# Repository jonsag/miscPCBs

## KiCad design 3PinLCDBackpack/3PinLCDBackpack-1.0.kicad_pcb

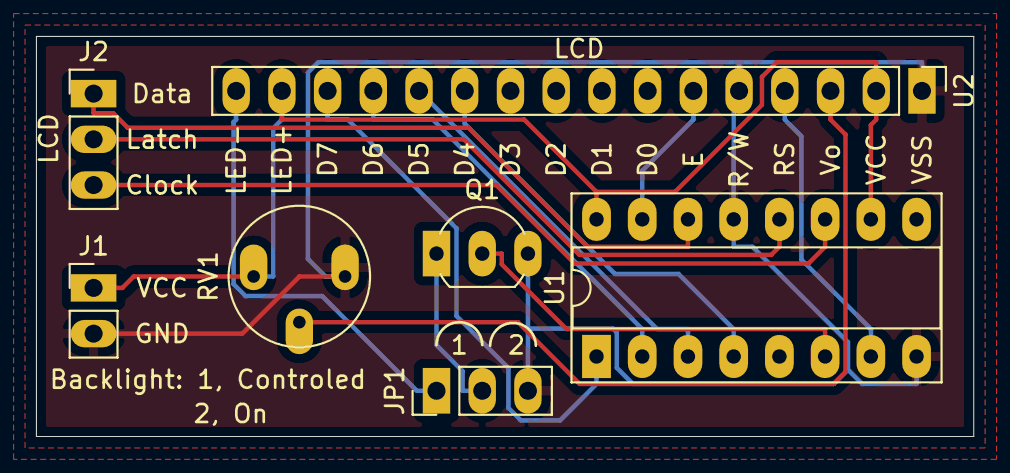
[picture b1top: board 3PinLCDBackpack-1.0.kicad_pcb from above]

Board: 2 copper layers, 52.1 x 22.2 mm, 7 parts (0 on the bottom side), 15 nets.

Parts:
J1: 2-pin_power_input_header; 2-pin_power_input_header_larger_pads
J2: 3-pin_LCD_header; 3-pin_LCD_header_larger_pads
JP1: Backlight control; Jumper_1x03_P2.54mm_large
Q1: BC547; TO-92_Inline_Wide_large
RV1: 10k; Potentiometer_Bourns_3339P_Vertical_large
U1: 74HC595; DIP-16_W7.62mm_Socket_LongPads
U2: LCD_HD44780; 16-pin_LCD_header_larger_pads

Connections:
/GND: J1.2, JP1.3, Q1.3, RV1.1, U1.8, U1.13, U2.1, U2.5
unnamed: J1.1, RV1.3, U1.10, U1.16, U2.2, U2.15
unnamed: J2.1, U1.14
unnamed: J2.2, U1.12
unnamed: J2.3, U1.11
unnamed: JP1.1, U2.16
unnamed: JP1.2, Q1.1
unnamed: Q1.2, U1.6
unnamed: RV1.2, U2.3
unnamed: U1.1, U2.14
unnamed: U1.2, U2.13
unnamed: U1.3, U2.12
unnamed: U1.4, U2.11
unnamed: U1.7, U2.4
unnamed: U1.15, U2.6

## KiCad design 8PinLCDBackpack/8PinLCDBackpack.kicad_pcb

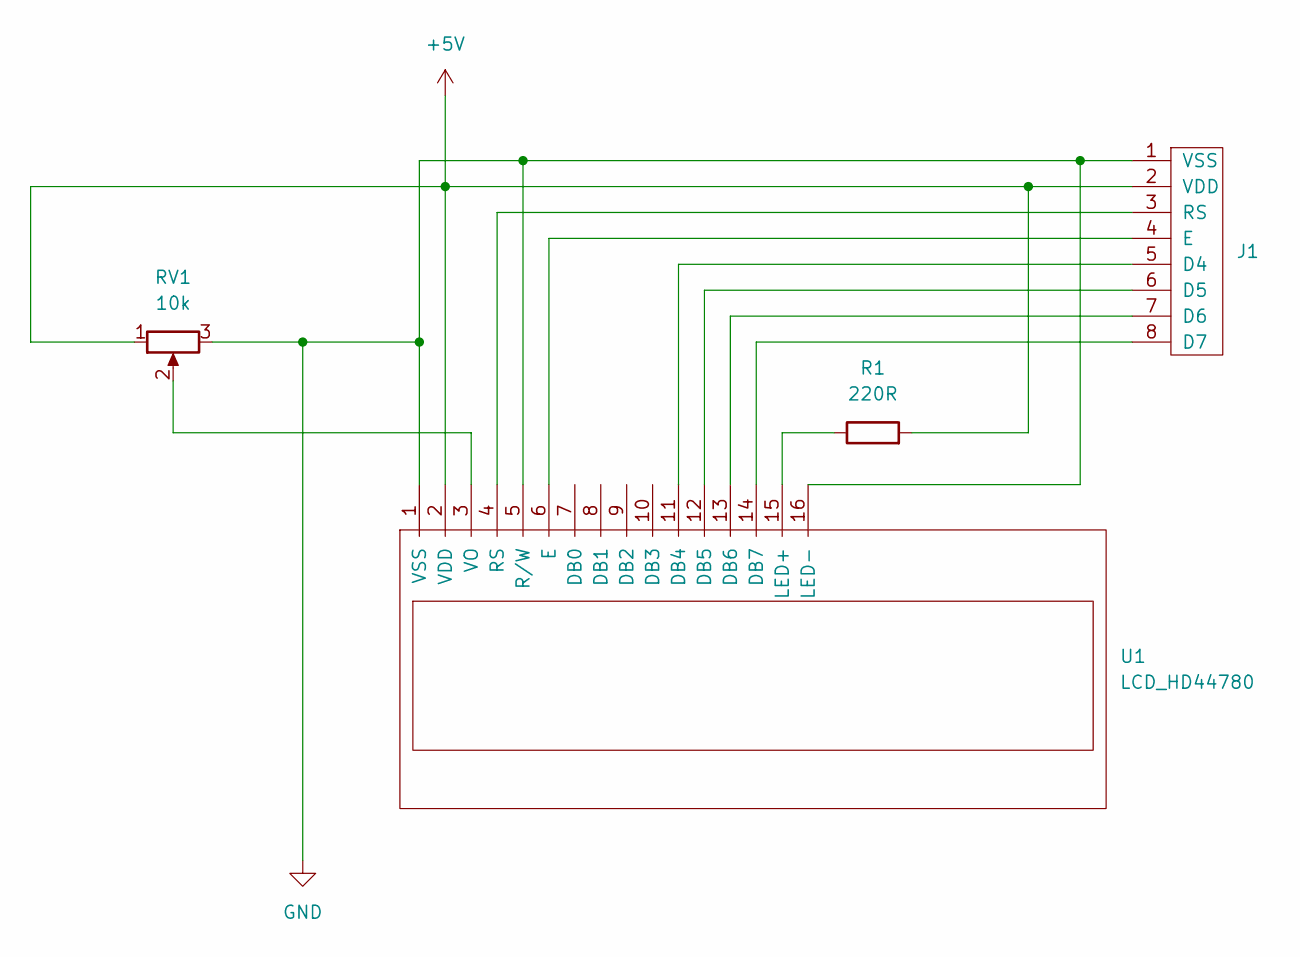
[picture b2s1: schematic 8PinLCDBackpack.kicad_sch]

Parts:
J1: 8-pin_header_LCD_interface; 8-pin JST LCD
R1: 220R; R_Axial_DIN0207_L6.3mm_D2.5mm_P10.16mm_Horizontal_larger_pa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
RV1: 10k; Potentiometer_Bourns_3339P_Vertical_large
U1: LCD_HD44780; LCD_HD44780_16x2_w_headers_large

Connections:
+5V: J1.2 (VDD), R1.2, RV1.1, U1.2 (VDD)
GND: J1.1 (VSS), RV1.3, U1.1 (VSS), U1.5 (R/W), U1.16 (LED-)
unnamed: J1.3 (RS), U1.4 (RS)
unnamed: J1.4 (E), U1.6 (E)
unnamed: J1.5 (D4), U1.11 (DB4)
unnamed: J1.6 (D5), U1.12 (DB5)
unnamed: J1.7 (D6), U1.13 (DB6)
unnamed: J1.8 (D7), U1.14 (DB7)
unnamed: R1.1, U1.15 (LED+)
unnamed: RV1.2, U1.3 (VO)

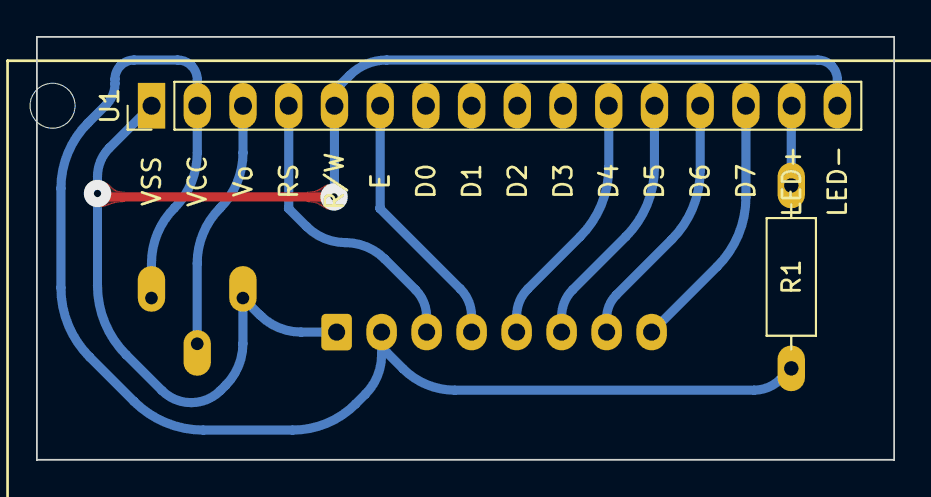
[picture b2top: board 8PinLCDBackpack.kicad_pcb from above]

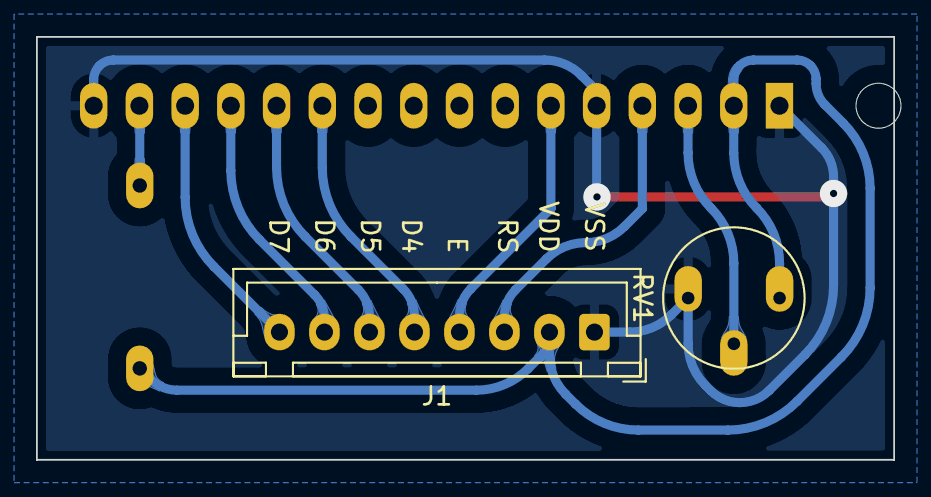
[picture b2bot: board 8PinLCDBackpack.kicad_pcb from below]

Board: 2 copper layers, 47.6 x 23.5 mm, 4 parts (2 on the bottom side), 10 nets.

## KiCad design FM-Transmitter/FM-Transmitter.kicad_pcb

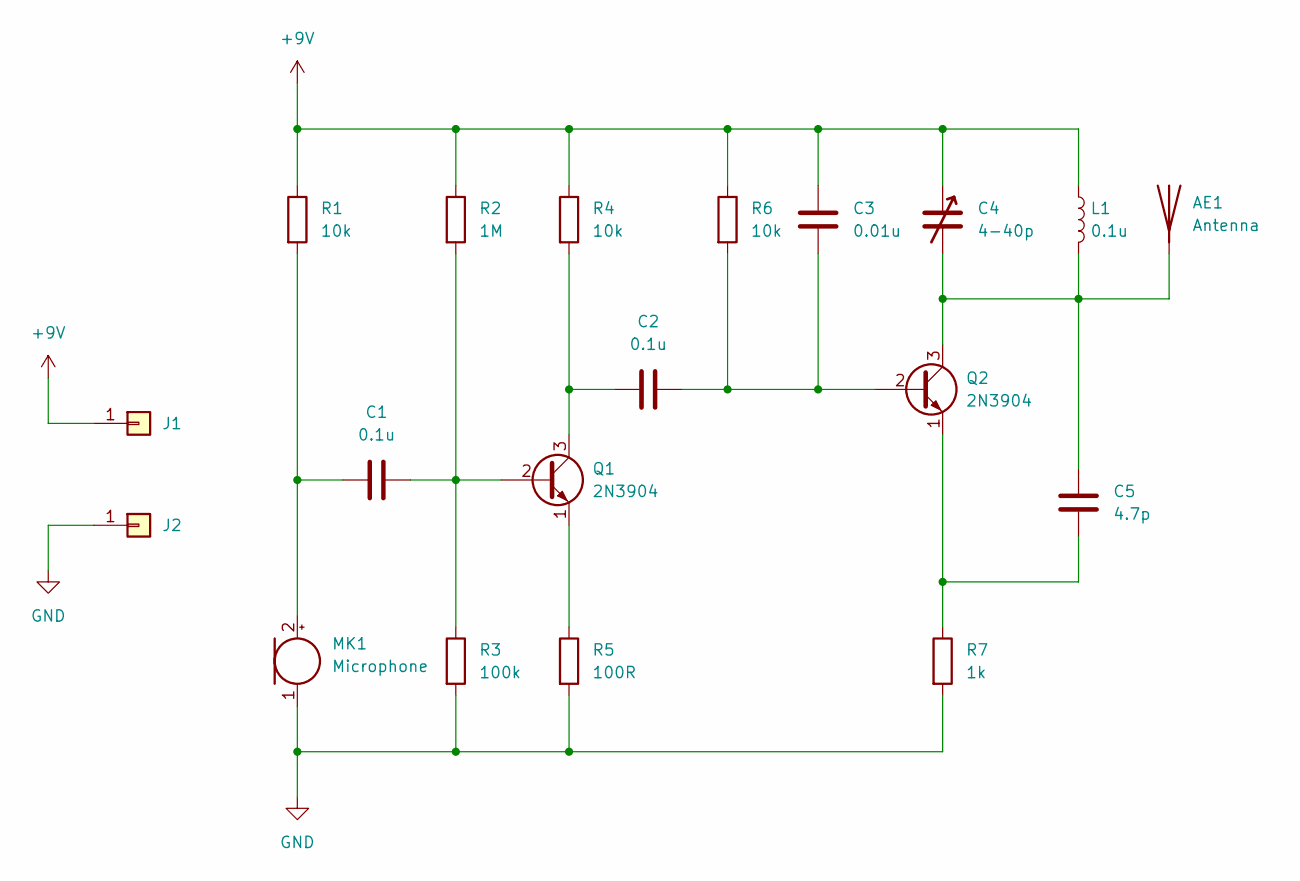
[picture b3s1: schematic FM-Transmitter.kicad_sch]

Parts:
AE1: Antenna; Single_solder_pad
C1, C2: 0.1u; C_Disc_D3.0mm_W1.6mm_P2.50mm_larg
C3: 0.01u; C_Disc_D3.0mm_W1.6mm_P2.50mm_larg
C4: 4-40p; JML06 Trim Capacitor
C5: 4.7p; C_Disc_D3.0mm_W1.6mm_P2.50mm_larg
J1, J2: Single_connector; Single_solder_pad
L1: 0.1u; Coil 10.16
MK1: Microphone; Electret Microphone D-6.3 H-4.3
Q1, Q2: 2N3904; TO-92_Inline_Wide_large
R1, R4, R6: 10k; R_Axial_DIN0207_L6.3mm_D2.5mm_P2.54mm_Vertical_large
R2: 1M; R_Axial_DIN0207_L6.3mm_D2.5mm_P2.54mm_Vertical_large
R3: 100k; R_Axial_DIN0207_L6.3mm_D2.5mm_P2.54mm_Vertical_large
R5: 100R; R_Axial_DIN0207_L6.3mm_D2.5mm_P2.54mm_Vertical_large
R7: 1k; R_Axial_DIN0207_L6.3mm_D2.5mm_P2.54mm_Vertical_large

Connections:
+9V: C3.2, C4.1, J1.1, L1.1, R1.1, R2.1, R4.1, R6.1
GND: J2.1, MK1.1 (-), R3.2, R5.2, R7.2
unnamed: AE1.1 (A), C4.2, C5.2, L1.2, Q2.3 (C)
unnamed: Q1.1 (E), R5.1
unnamed: C5.1, Q2.1 (E), R7.1
unnamed: C1.1, MK1.2 (+), R1.2
unnamed: C1.2, Q1.2 (B), R2.2, R3.1
unnamed: C2.1, Q1.3 (C), R4.2
unnamed: C2.2, C3.1, Q2.2 (B), R6.2

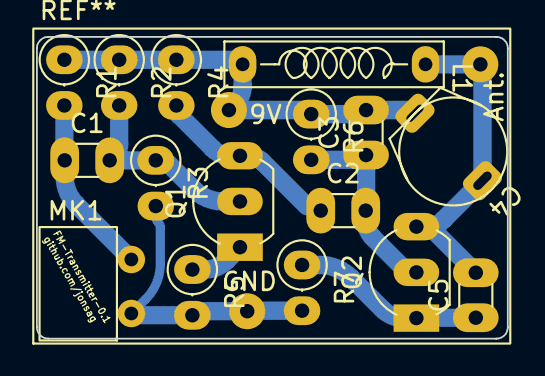
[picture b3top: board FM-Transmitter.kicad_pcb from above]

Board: 2 copper layers, 26.2 x 16.8 mm, 19 parts (0 on the bottom side), 9 nets.

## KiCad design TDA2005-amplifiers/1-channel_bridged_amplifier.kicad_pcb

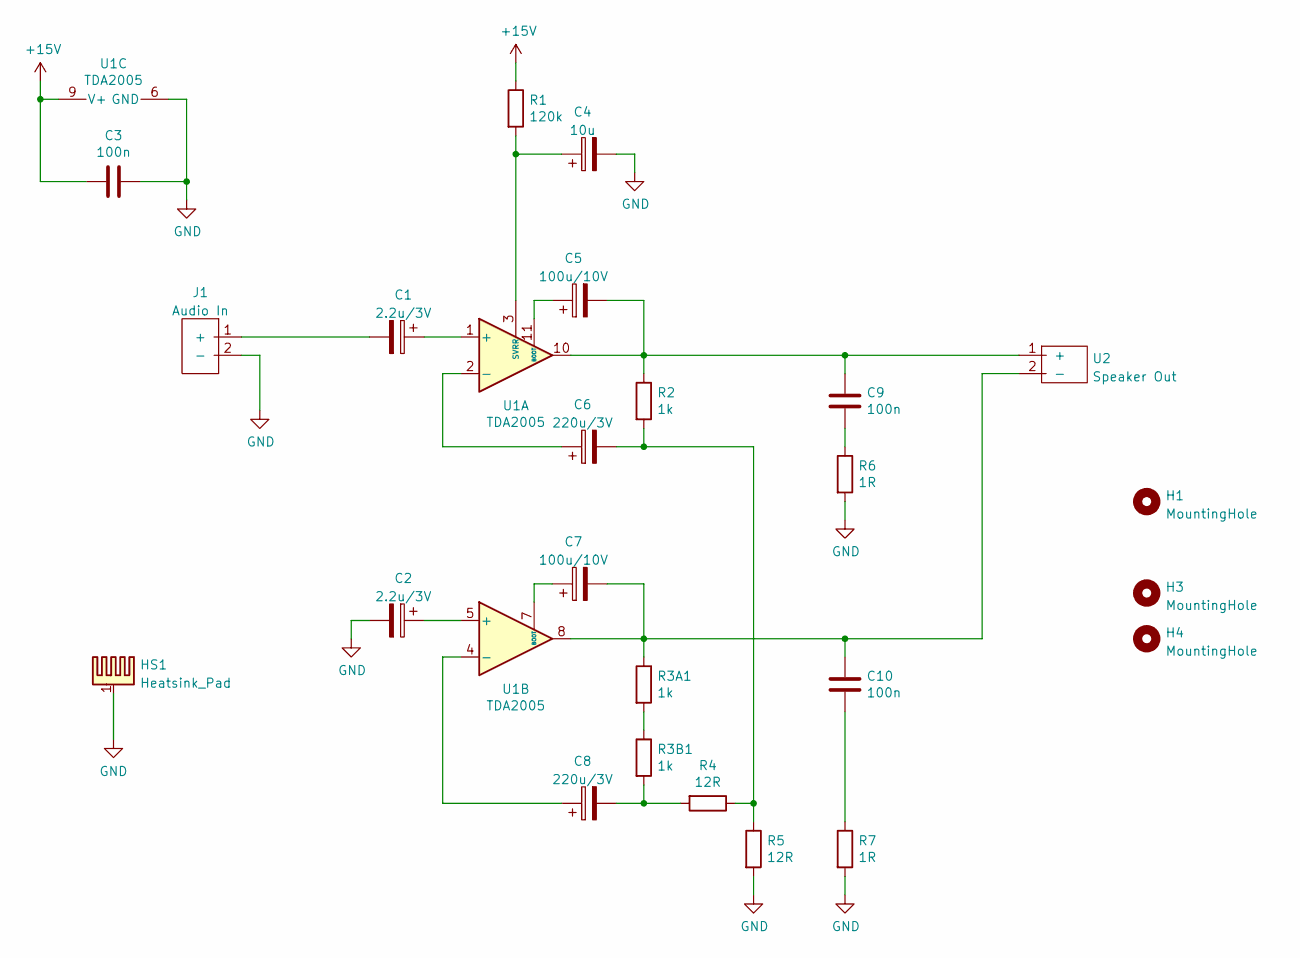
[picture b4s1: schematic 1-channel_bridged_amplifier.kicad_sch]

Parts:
C1, C2: 2.2u/3V; CP_Radial_D5.0mm_P2.00mm_larger
C3, C9, C10: 100n; C_Disc_D7.5mm_W2.5mm_P5.00mm_larger
C4: 10u; CP_Radial_D5.0mm_P2.00mm_larger
C5, C7: 100u/10V; CP_Radial_D8.0mm_P3.50mm_large
C6, C8: 220u/3V; CP_Radial_D10.0mm_P5.00mm_larger
H1, H3, H4: MountingHole; MountingHole_3.2mm_M3
HS1: Heatsink_Pad; EK-41002859
J1: Audio In; 2-pin JST Audio
R1: 120k; R_Axial_DIN0414_L11.9mm_D4.5mm_P15.24mm_Horizontal_larger
R2, R3A1, R3B1: 1k; R_Axial_DIN0414_L11.9mm_D4.5mm_P15.24mm_Horizontal_larger
R4, R5: 12R; R_Axial_DIN0414_L11.9mm_D4.5mm_P15.24mm_Horizontal_larger
R6, R7: 1R; R_Axial_DIN0414_L11.9mm_D4.5mm_P15.24mm_Horizontal_larger
U1: TDA2005; TO-220-11_P3.4x5.08mm_StaggerOdd_Lead4.85mm_Vertical_large
U2: Speaker Out; 2-pole_power_in_screw_terminal

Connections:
+15V: C3.2, R1.1, U1.9 (V+)
GND: C2.2, C3.1, C4.2, HS1.1, J1.2 (-), R5.2, R6.2, R7.2, U1.6 (GND)
unnamed: C1.2, J1.1 (+)
unnamed: C5.2, C9.1, R2.1, U1.10, U2.1 (+)
unnamed: C9.2, R6.1
unnamed: C7.2, C10.1, R3A1.1, U1.8, U2.2 (-)
unnamed: C10.2, R7.1
unnamed: C4.1, R1.2, U1.3 (SVRR)
unnamed: C6.2, R2.2, R4.1, R5.1
unnamed: R3A1.2, R3B1.1
unnamed: C8.2, R3B1.2, R4.2
unnamed: C1.1, U1.1 (+)
unnamed: C6.1, U1.2 (-)
unnamed: C8.1, U1.4 (-)
unnamed: C2.1, U1.5 (+)
unnamed: C7.1, U1.7 (BOOT)
unnamed: C5.1, U1.11 (BOOT)

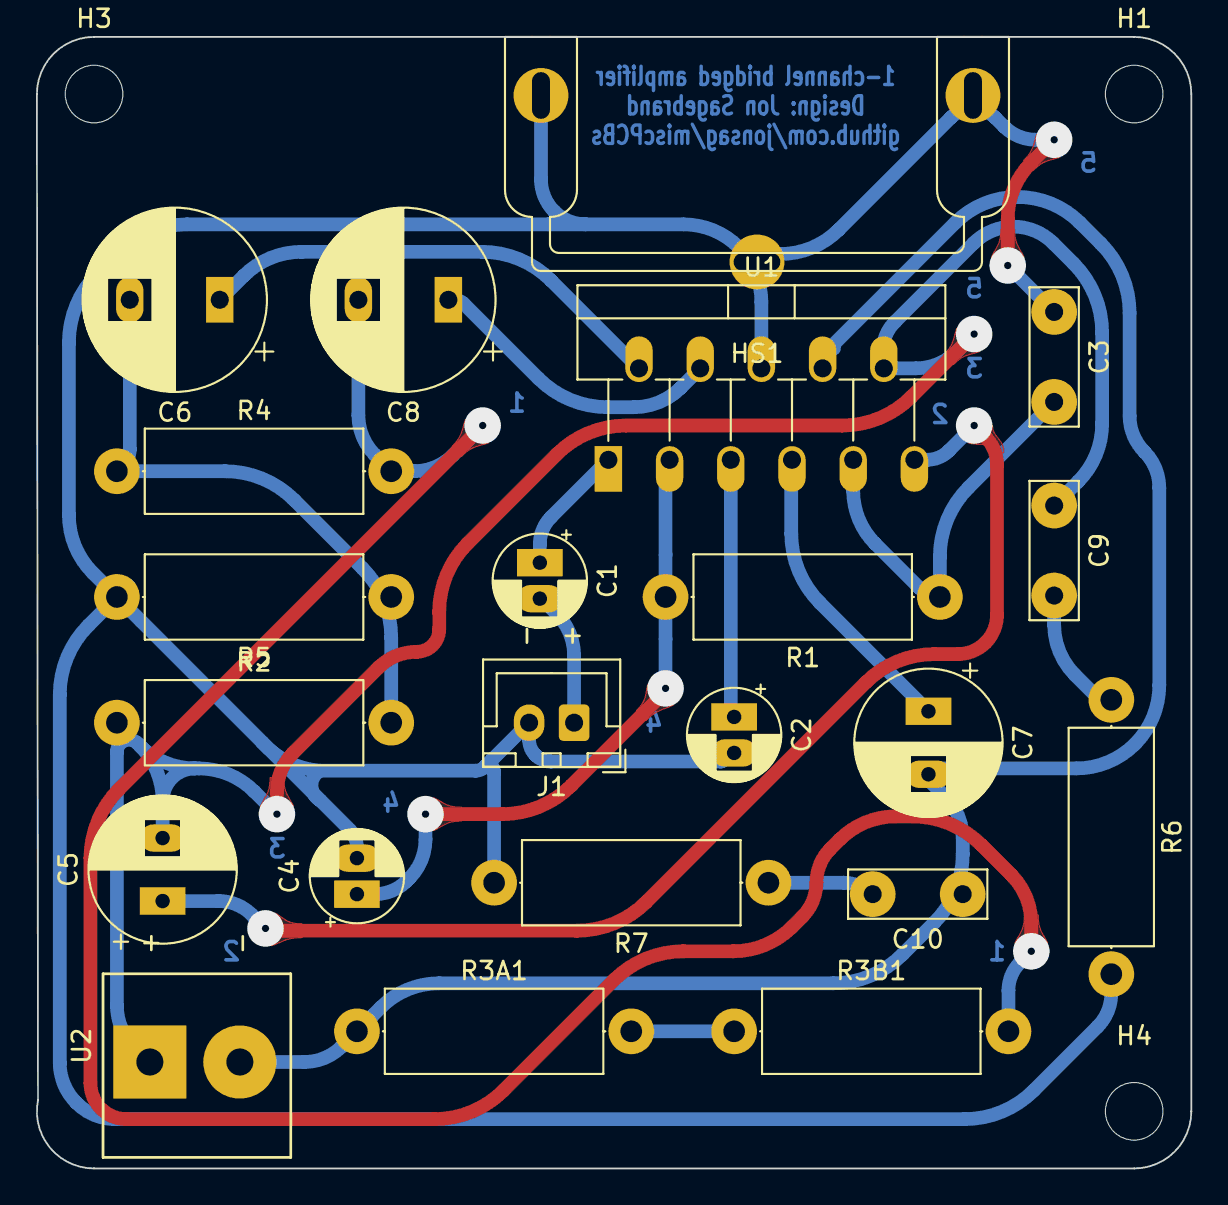
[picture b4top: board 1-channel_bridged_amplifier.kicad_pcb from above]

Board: 2 copper layers, 64.1 x 62.9 mm, 25 parts (0 on the bottom side), 17 nets.

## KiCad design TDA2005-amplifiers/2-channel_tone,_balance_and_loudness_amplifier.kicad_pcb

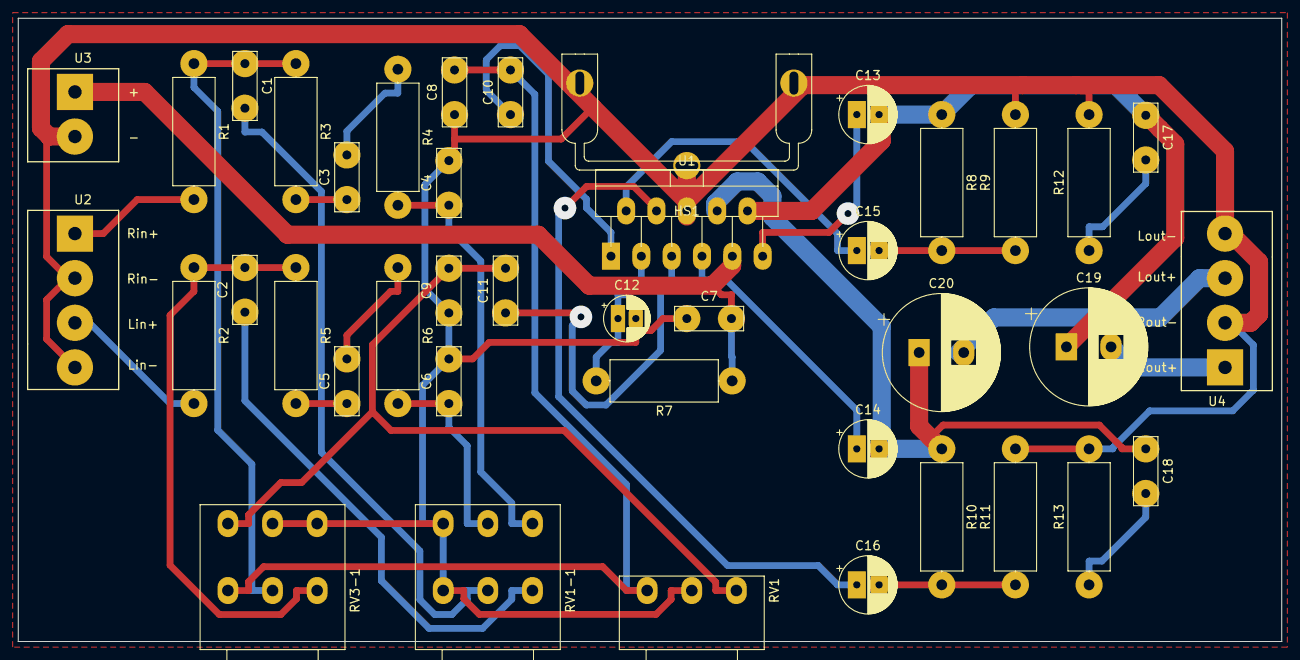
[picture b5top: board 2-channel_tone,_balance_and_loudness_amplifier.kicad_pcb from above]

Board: 2 copper layers, 141.6 x 69.8 mm, 41 parts (0 on the bottom side), 31 nets.

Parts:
C1, C2: 47n; C_Disc_D7.5mm_W2.5mm_P5.00mm_larger
C3, C5, C8, C9: 2.2n; C_Disc_D7.5mm_W2.5mm_P5.00mm_larger
C4, C6: 150n; C_Disc_D7.5mm_W2.5mm_P5.00mm_larger
C7, C17, C18: 100n; C_Disc_D7.5mm_W2.5mm_P5.00mm_larger
C10, C11: 220n; C_Disc_D7.5mm_W2.5mm_P5.00mm_larger
C12: 10u; CP_Radial_D5.0mm_P2.00mm_larger
C13, C14, C15, C16: 100u; CP_Radial_D6.3mm_P2.50mm_large
C19, C20: 2200u; CP_Radial_D13.0mm_P5.00mm_larger
HS1: Heatsink_Pad; EK-41002859
R1, R2: 5.6k; R_Axial_DIN0414_L11.9mm_D4.5mm_P15.24mm_Horizontal_larger
R3, R5: 47k; R_Axial_DIN0414_L11.9mm_D4.5mm_P15.24mm_Horizontal_larger
R4, R6: 2.7k; R_Axial_DIN0414_L11.9mm_D4.5mm_P15.24mm_Horizontal_larger
R7: 120k; R_Axial_DIN0414_L11.9mm_D4.5mm_P15.24mm_Horizontal_larger
R8, R10: 100k; R_Axial_DIN0414_L11.9mm_D4.5mm_P15.24mm_Horizontal_larger
R9, R11: 3.3R; R_Axial_DIN0414_L11.9mm_D4.5mm_P15.24mm_Horizontal_larger
R12, R13: 1R; R_Axial_DIN0414_L11.9mm_D4.5mm_P15.24mm_Horizontal_larger
RV1: 100k; Potentiometer_Piher_PC-16_Single_Horizontal_larger
RV1-1, RV3-1: Dual_potentiometer; Potentiometer_Piher_PC-16_Dual_Horizontal_larger
U1: TDA2005; TO-220-11_P3.4x5.08mm_StaggerOdd_Lead4.85mm_Vertical_large
U2: 4-pole_RL-input_screw_terminal; 4-pole_screw_terminal_RL_input
U3: 2-pole_power_in_screw_terminal
U4: 4-pole_RL-output_screw_terminal; 4-pole_screw_terminal_RL_output

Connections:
+15V: C7.2, R7.1, U1.9, U3.1
GND: C4.2, C6.2, C7.1, C8.1, C9.1, C12.2, HS1.1, R9.2, R11.2, R12.2, R13.2, RV1.2, RV1-1.1, RV1-1.4, RV3-1.5, RV3-1.6, U1.6, U2.2, U2.4, U3.2, U4.2, U4.4
Lin+: R2.2, U2.3
Lout+: C20.2, U4.3
unnamed: C1.1, R1.1, R3.1, RV3-1.2
unnamed: C1.2, RV1-1.2
unnamed: C2.1, RV1-1.3
unnamed: C2.2, R2.1, R5.1, RV3-1.3
unnamed: C3.1, R3.2
unnamed: C3.2, R4.1
unnamed: C4.1, R4.2, RV1-1.6
unnamed: C5.1, R5.2
unnamed: C5.2, R6.1
unnamed: C6.1, R6.2, RV1-1.5
unnamed: C10.1, U1.1
unnamed: C8.2, C10.2, RV1.1, RV3-1.1
unnamed: C11.1, U1.5
unnamed: C9.2, C11.2, RV1.3, RV3-1.4
unnamed: C12.1, R7.2, U1.3
unnamed: C13.1, U1.11
unnamed: C13.2, C17.1, C19.1, R8.1, U1.10
unnamed: C14.1, U1.7
unnamed: C14.2, C18.1, C20.1, R10.1, U1.8
unnamed: C15.1, U1.2
unnamed: C15.2, R8.2, R9.1
unnamed: C16.1, U1.4
unnamed: C16.2, R10.2, R11.1
unnamed: C17.2, R12.1
unnamed: C18.2, R13.1
Rin+: R1.2, U2.1
Rout+: C19.2, U4.1

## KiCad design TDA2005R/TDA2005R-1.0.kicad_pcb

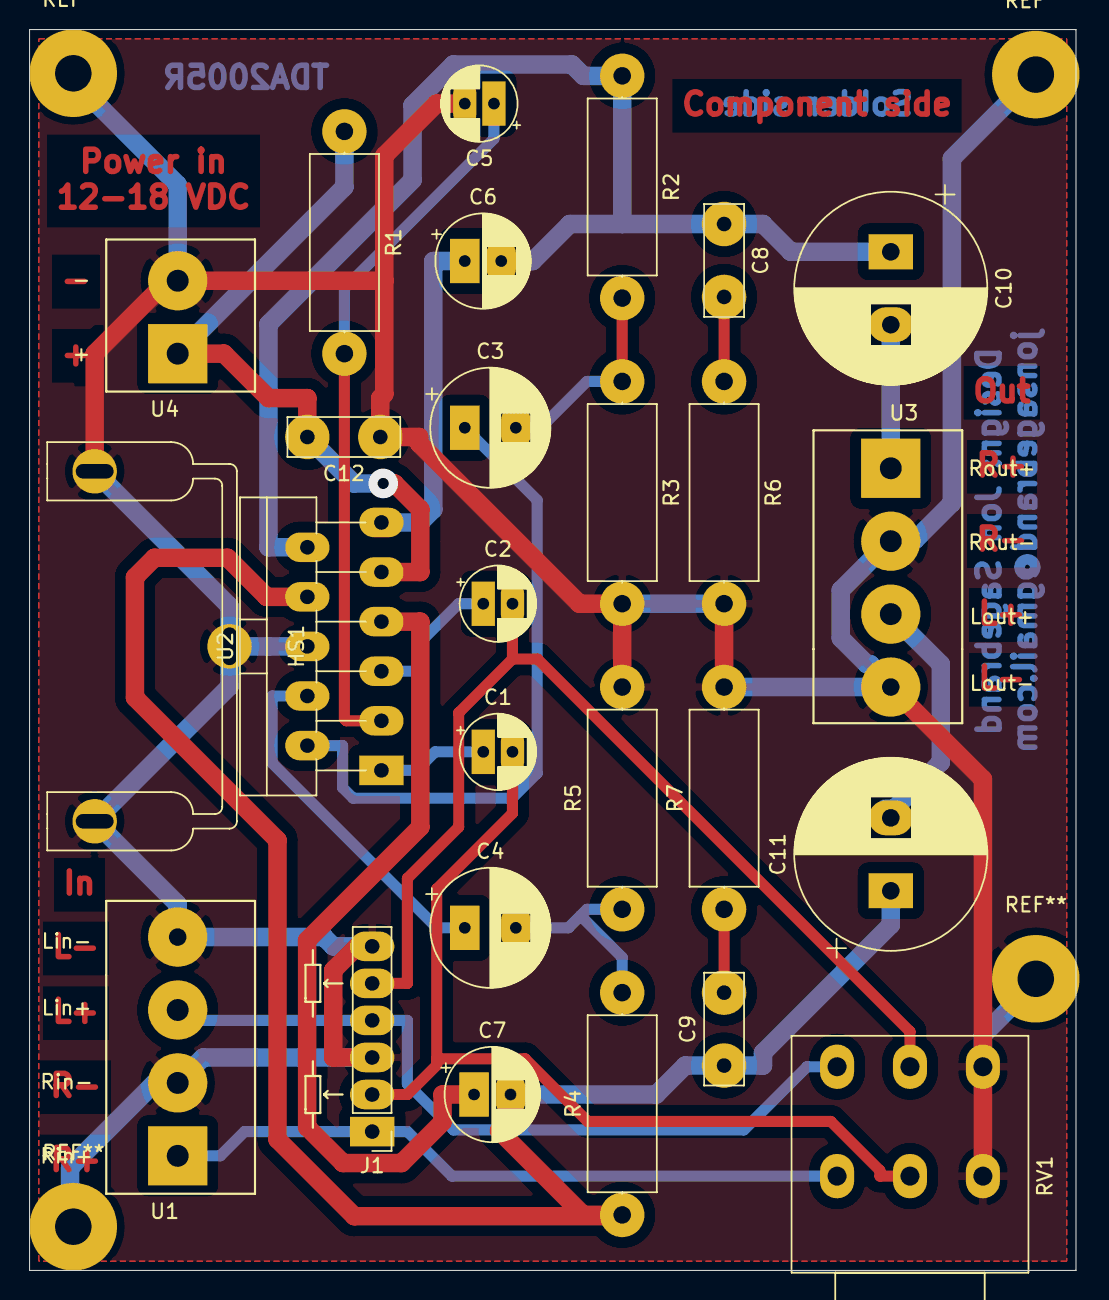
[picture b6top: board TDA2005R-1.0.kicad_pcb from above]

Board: 2 copper layers, 71.8 x 85.1 mm, 26 parts (0 on the bottom side), 21 nets.

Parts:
C1, C2: 2.2u; CP_Radial_D5.0mm_P2.00mm_larger
C3, C4: 220u; CP_Radial_D8.0mm_P3.50mm_large
C5: 10u; CP_Radial_D5.0mm_P2.00mm_larger
C6, C7: 100u; CP_Radial_D6.3mm_P2.50mm_large
C8, C9, C12: 0.1u; C_Disc_D7.5mm_W2.5mm_P5.00mm_larger
C10, C11: 2200u; CP_Radial_D13.0mm_P5.00mm_larger
HS1: Heatsink_Pad; EK-41002859
J1: 6-pole_dual_potentiometer_header; 6-pin_dual_potentiometer_header_large
R1: 120k; R_Axial_DIN0414_L11.9mm_D4.5mm_P15.24mm_Horizontal_larger
R2, R4: 1.2k; R_Axial_DIN0414_L11.9mm_D4.5mm_P15.24mm_Horizontal_larger
R3, R5: 33R; R_Axial_DIN0414_L11.9mm_D4.5mm_P15.24mm_Horizontal_larger
R6, R7: 1R; R_Axial_DIN0414_L11.9mm_D4.5mm_P15.24mm_Horizontal_larger
RV1: R_POT_Dual; Potentiometer_Piher_PC-16_Dual_Horizontal_larger
U1: 4-pole_RL-input_screw_terminal; 4-pole_screw_terminal_RL_input
U2: TDA2005; TO-220-11_P3.4x5.08mm_StaggerOdd_Lead4.85mm_Vertical_large
U3: 4-pole_RL-output_screw_terminal; 4-pole_screw_terminal_RL_output
U4: 2-pole_power_in_screw_terminal

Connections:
+15V: C12.2, R1.1, U2.9, U4.1
GND: C5.2, C12.1, HS1.1, J1.3, J1.6, R3.2, R5.2, R6.2, R7.2, RV1.3, RV1.6, U1.2, U1.4, U2.6, U3.2, U3.4, U4.2
Lin: J1.4, RV1.4, U1.3
Lout: C11.2, U3.3
unnamed: C1.1, U2.1
unnamed: C1.2, J1.2, RV1.2
unnamed: C2.1, U2.5
unnamed: C2.2, J1.5, RV1.5
unnamed: C3.1, U2.2
unnamed: C3.2, R2.2, R3.1
unnamed: C4.1, U2.4
unnamed: C4.2, R4.2, R5.1
unnamed: C5.1, R1.2, U2.3
unnamed: C6.1, U2.11
unnamed: C7.1, U2.7
unnamed: C8.2, R6.1
unnamed: C9.2, R7.1
unnamed: C6.2, C8.1, C10.1, R2.1, U2.10
unnamed: C7.2, C9.1, C11.1, R4.1, U2.8
Rin: J1.1, RV1.1, U1.1
Rout: C10.2, U3.1
